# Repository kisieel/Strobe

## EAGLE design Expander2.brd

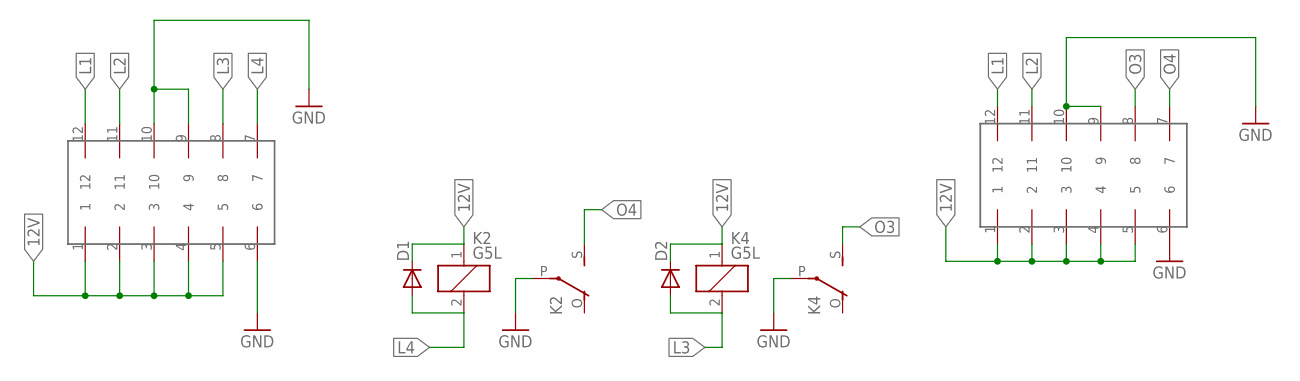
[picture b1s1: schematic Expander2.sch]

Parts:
D1, D2: DIODESMB; SMB-DIODE
IN: MF42-10
K2, K4: G5L; G5LE
OUT: MF42-10

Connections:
12V: D1.C, D2.C, IN.1, IN.2, IN.3, IN.4, IN.5, K2.1, K4.1, OUT.1, OUT.2, OUT.3, OUT.4, OUT.5
GND: IN.6, IN.9, IN.10, K2.P, K4.P, OUT.6, OUT.9, OUT.10
L1: IN.12, OUT.12
L2: IN.11, OUT.11
L3: D2.A, IN.8, K4.2
L4: D1.A, IN.7, K2.2
O3: K4.S, OUT.8
O4: K2.S, OUT.7

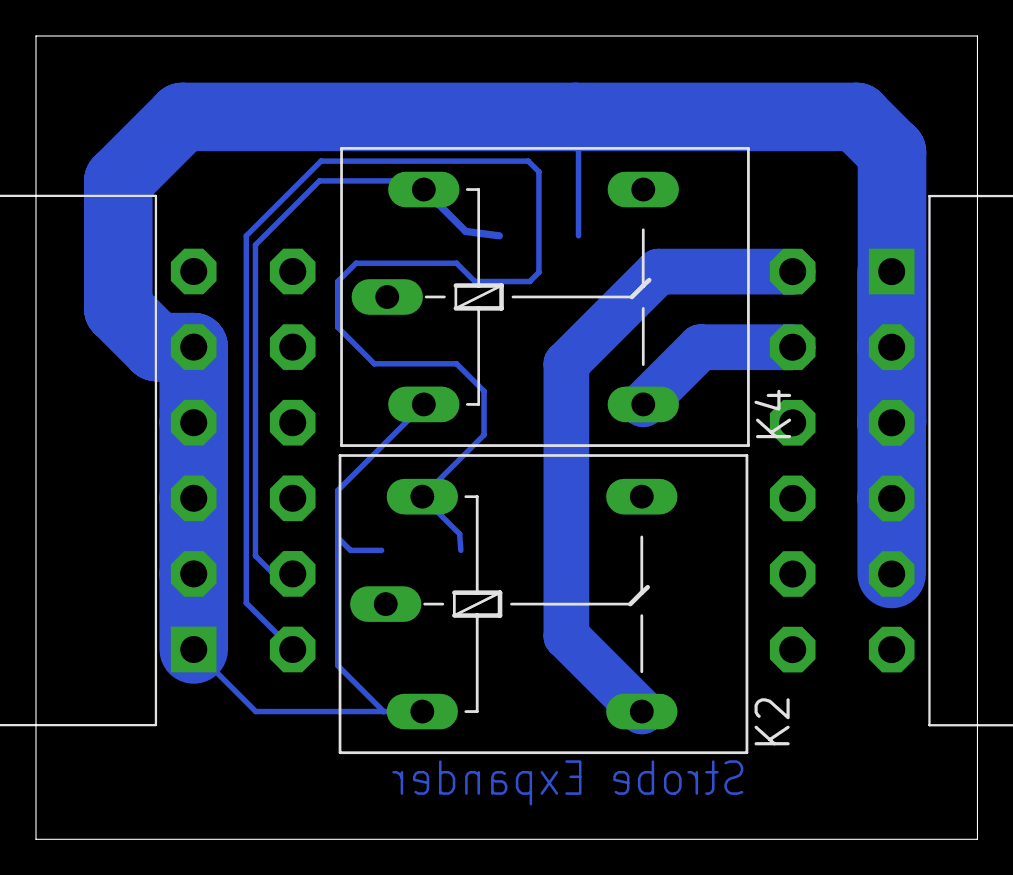
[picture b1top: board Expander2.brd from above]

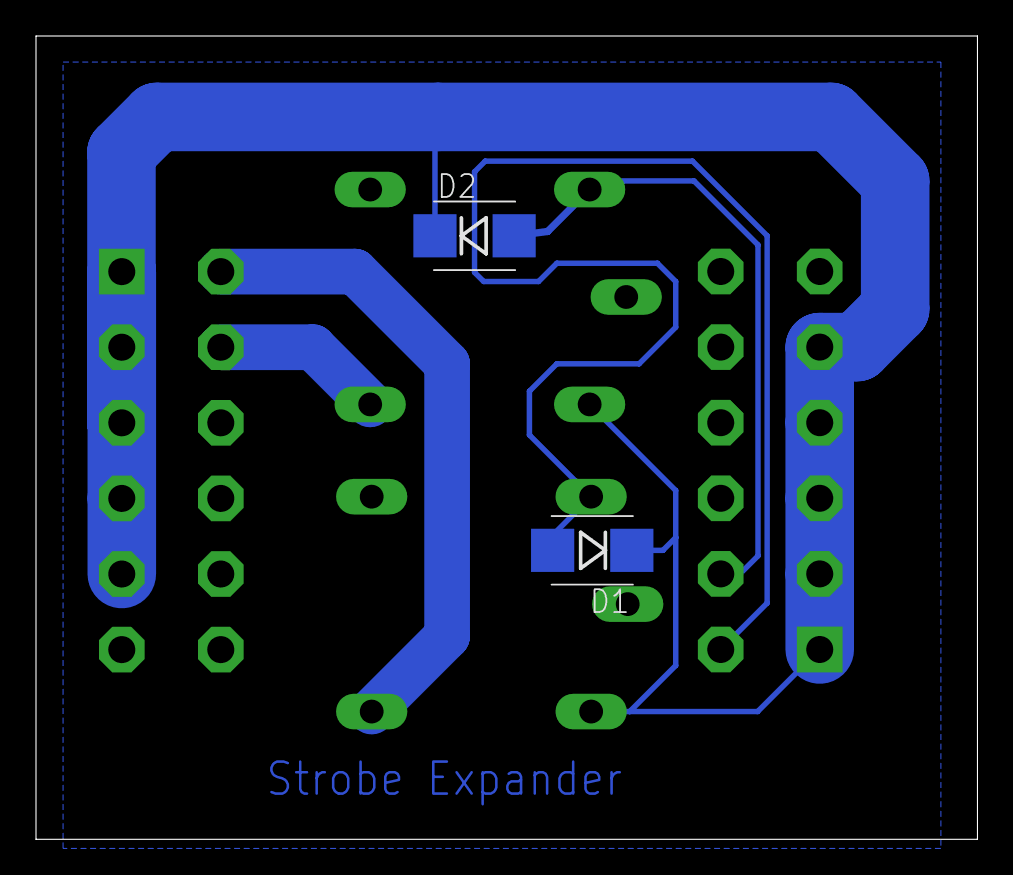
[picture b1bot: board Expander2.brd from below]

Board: 2 copper layers, 52.3 x 44.6 mm, 6 parts (2 on the bottom side), 8 nets.

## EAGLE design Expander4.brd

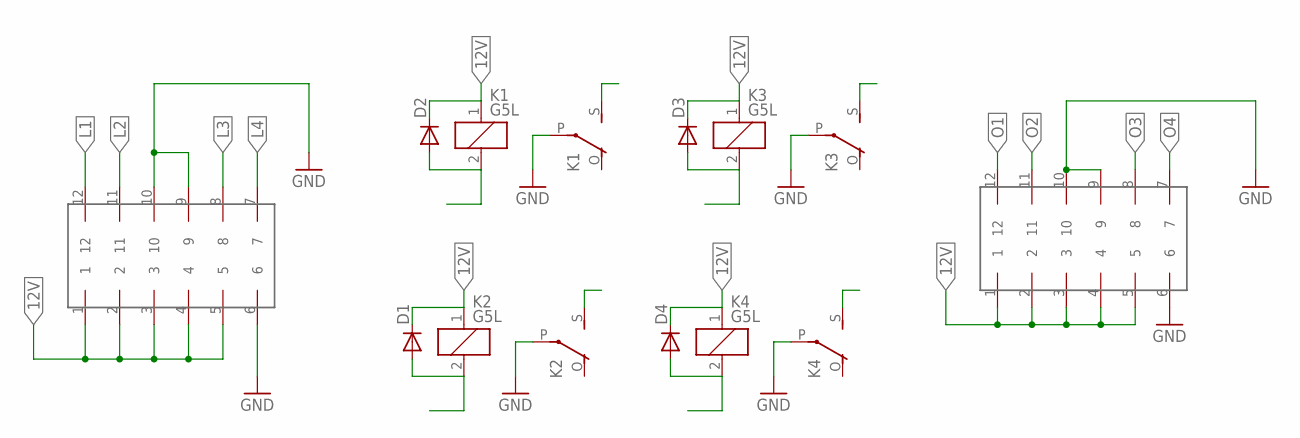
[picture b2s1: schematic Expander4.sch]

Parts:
D1, D2, D3, D4: DIODESMB; SMB-DIODE
IN: MF42-10
K1, K2, K3, K4: G5L; G5LE
OUT: MF42-10

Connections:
12V: D1.C, D2.C, D3.C, D4.C, IN.1, IN.2, IN.3, IN.4, IN.5, K1.1, K2.1, K3.1, K4.1, OUT.1, OUT.2, OUT.3, OUT.4, OUT.5
GND: IN.6, IN.9, IN.10, K1.P, K2.P, K3.P, K4.P, OUT.6, OUT.9, OUT.10
L1: D2.A, IN.12, K1.2
L2: D1.A, IN.11, K2.2
L3: D3.A, IN.8, K3.2
L4: D4.A, IN.7, K4.2
O1: K1.S, OUT.12
O2: K2.S, OUT.11
O3: K3.S, OUT.8
O4: K4.S, OUT.7

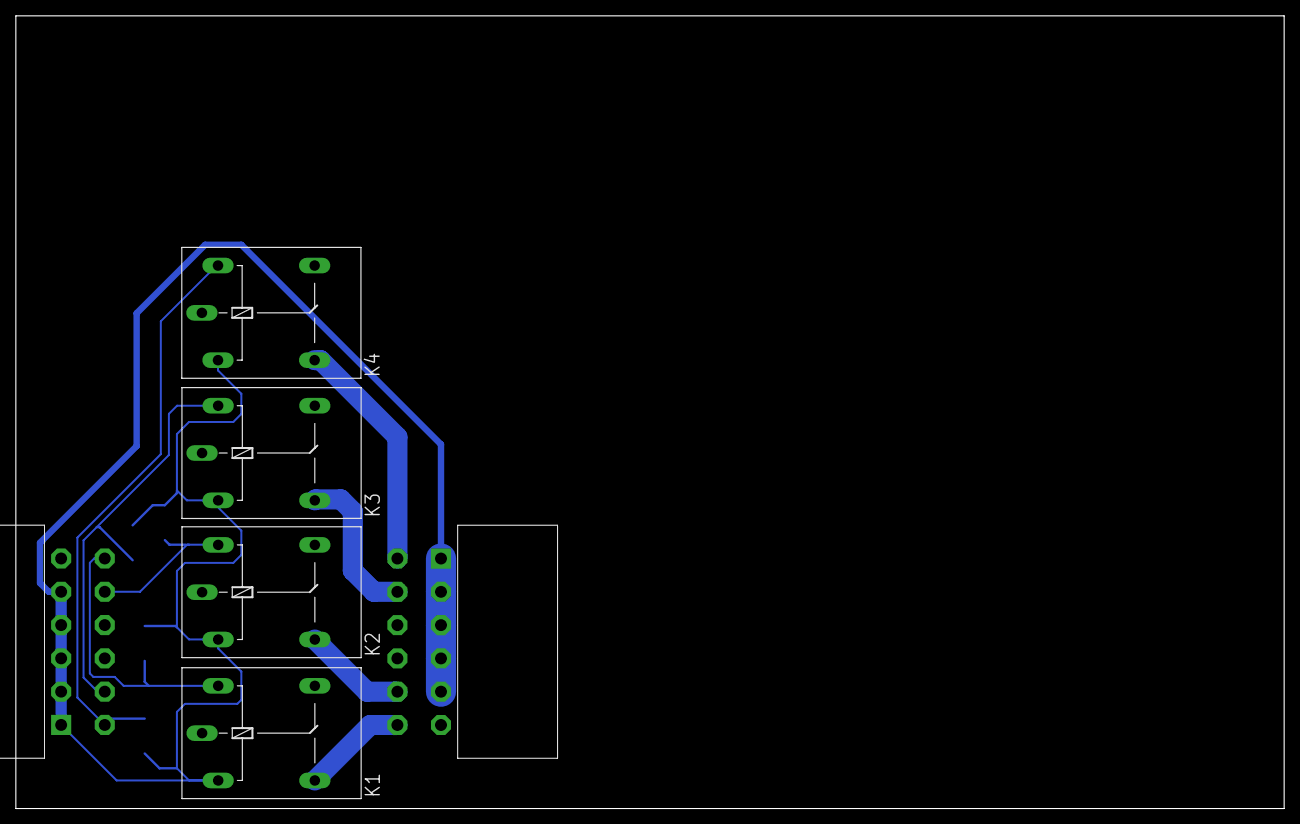
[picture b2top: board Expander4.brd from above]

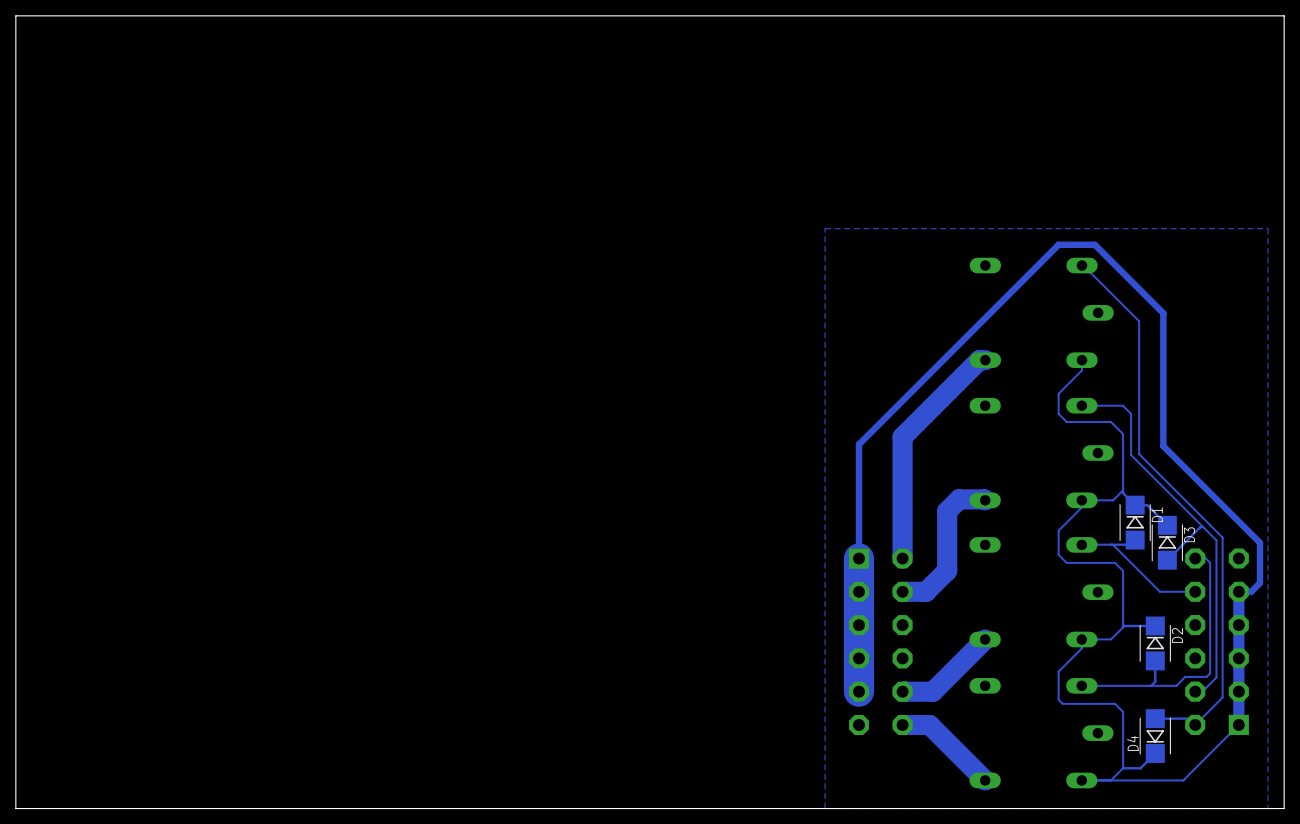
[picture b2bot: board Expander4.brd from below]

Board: 2 copper layers, 160.0 x 100.0 mm, 10 parts (4 on the bottom side), 10 nets.

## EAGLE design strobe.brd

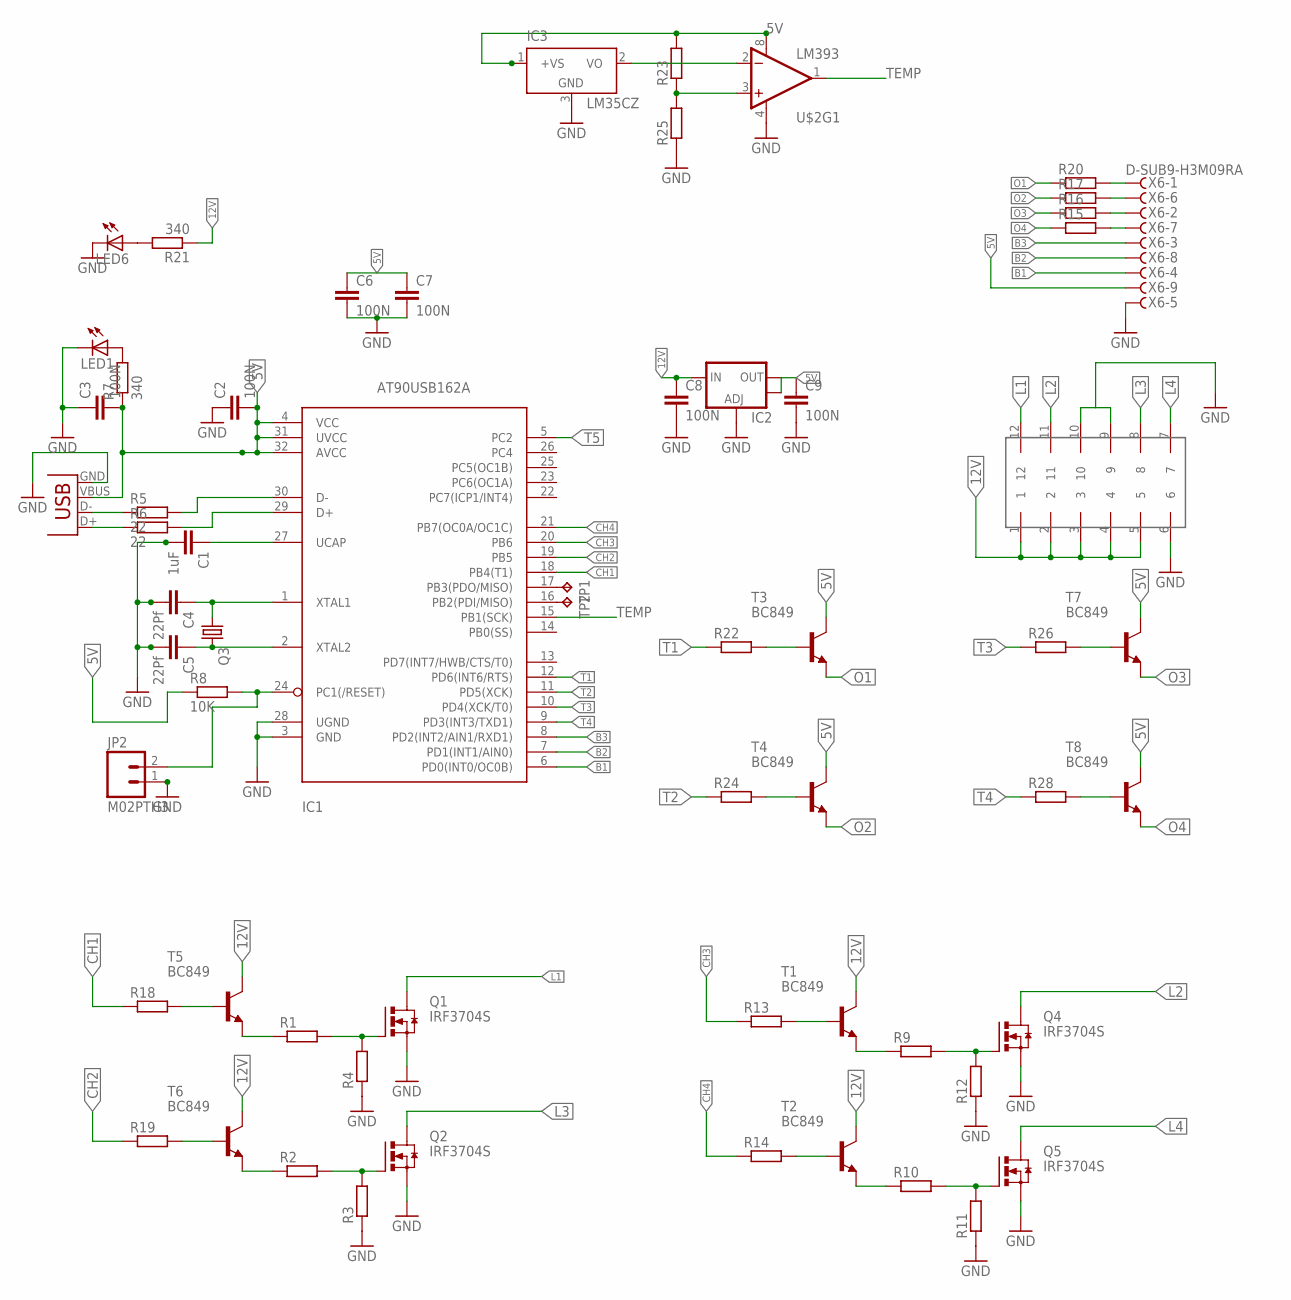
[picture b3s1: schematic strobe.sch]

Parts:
C1: 1uF; C0805
C2, C3, C6, C7, C8, C9: 100N; C0805
C4, C5: 22Pf; C0603
IC1: AT90USB162A; TQFP32-08
IC2: V_REG_LM1117SOT223; SOT223
IC3: LM35CZ; TO92
JP1: USB-B; USB-B-PTH
JP2: M02PTH3; 1X02_LONGPADS
LED1, LED6: LEDSML0805; SML0805
Q1, Q2, Q4, Q5: IRF3704S; D2PACK
Q3: CRYSTALSM49; SM49
R1, R2, R3, R4, R9, R10, R11, R12, R13, R14, R15, R16, R17, R18, R19, R20, R22, R24, R26, R28: R-EU_R0805; R0805
R5, R6: 22; R0805
R7, R21: 340; R0805
R8: 10K; R0805
R23, R25: R-EU_M0805; M0805
T1, T2, T3, T4, T5, T6, T7, T8: BC849; SOT23
TP1, TP2: TPB1,27; B1,27
U$1: MF42-10
U$2: LM393; SO08
X6: D-SUB9-H3M09RA; H3M09RA

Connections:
5V: C2.2, C3.2, C6.1, C7.1, C9.1, IC1.4 (VCC), IC1.31 (UVCC), IC1.32 (AVCC), IC2.2 (OUT), IC2.4 (OUT), IC3.1 (+VS), JP1.VBUS, R7.1, R8.1, R23.2, T3.3 (C), T4.3 (C), T7.3 (C), T8.3 (C), U$2.8 (V+), X6.9
12V: C8.1, IC2.3 (IN), R21.1, T1.3 (C), T2.3 (C), T5.3 (C), T6.3 (C), U$1.1, U$1.2, U$1.3, U$1.4, U$1.5
B1: IC1.6 (PD0(INT0/OC0B)), X6.4
B2: IC1.7 (PD1(INT1/AIN0)), X6.8
B3: IC1.8 (PD2(INT2/AIN1/RXD1)), X6.3
CH1: IC1.18 (PB4(T1)), R18.1
CH2: IC1.19 (PB5), R19.1
CH3: IC1.20 (PB6), R13.1
CH4: IC1.21 (PB7(OC0A/OC1C)), R14.1
GND: C1.2, C2.1, C3.1, C4.2, C5.2, C6.2, C7.2, C8.2, C9.2, IC1.3 (GND), IC1.28 (UGND), IC2.1 (ADJ), IC3.3 (GND), JP1.GND, JP2.1, LED1.C, LED6.C, Q1.3 (S), Q2.3 (S), Q4.3 (S), Q5.3 (S), R3.1, R4.1, R11.1, R12.1, R25.1, U$1.6, U$1.9, U$1.10, U$2.4 (V-), X6.5
L1: Q1.2 (D), U$1.12
L2: Q4.2 (D), U$1.11
L3: Q2.2 (D), U$1.8
L4: Q5.2 (D), U$1.7
unnamed: Q1.1 (G), R1.2, R4.2
unnamed: Q2.1 (G), R2.2, R3.2
unnamed: IC3.2 (VO), U$2.2 (-IN)
unnamed: R23.1, R25.2, U$2.3 (+IN)
unnamed: C1.1, IC1.27 (UCAP)
unnamed: JP1.D+, R6.1
unnamed: JP1.D-, R5.1
unnamed: IC1.30 (D-), R5.2
unnamed: IC1.29 (D+), R6.2
unnamed: LED1.A, R7.2
unnamed: Q4.1 (G), R9.2, R12.2
unnamed: C5.1, IC1.2 (XTAL2), Q3.2
unnamed: C4.1, IC1.1 (XTAL1), Q3.1
unnamed: IC1.24 (PC1(/RESET)), JP2.2, R8.2
unnamed: Q5.1 (G), R10.2, R11.2
unnamed: R9.1, T1.2 (E)
unnamed: R10.1, T2.2 (E)
unnamed: R13.2, T1.1 (B)
unnamed: R14.2, T2.1 (B)
unnamed: IC1.17 (PB3(PDO/MISO)), TP1.TP
unnamed: LED6.A, R21.2
unnamed: R22.2, T3.1 (B)
unnamed: IC1.16 (PB2(PDI/MISO)), TP2.TP
unnamed: R20.2, X6.1
unnamed: R24.2, T4.1 (B)
unnamed: R1.1, T5.2 (E)
unnamed: R2.1, T6.2 (E)
unnamed: R18.2, T5.1 (B)
unnamed: R19.2, T6.1 (B)
unnamed: R17.2, X6.6
unnamed: R26.2, T7.1 (B)
unnamed: R16.2, X6.2
unnamed: R15.2, X6.7
unnamed: R28.2, T8.1 (B)
O1: R20.1, T3.2 (E)
O2: R17.1, T4.2 (E)
O3: R16.1, T7.2 (E)
O4: R15.1, T8.2 (E)
T1: IC1.12 (PD6(INT6/RTS)), R22.1
T2: IC1.11 (PD5(XCK)), R24.1
T3: IC1.10 (PD4(XCK/T0)), R26.1
T4: IC1.9 (PD3(INT3/TXD1)), R28.1
T5: IC1.5 (PC2)
TEMP: IC1.15 (PB1(SCK)), U$2.1 (OUT)

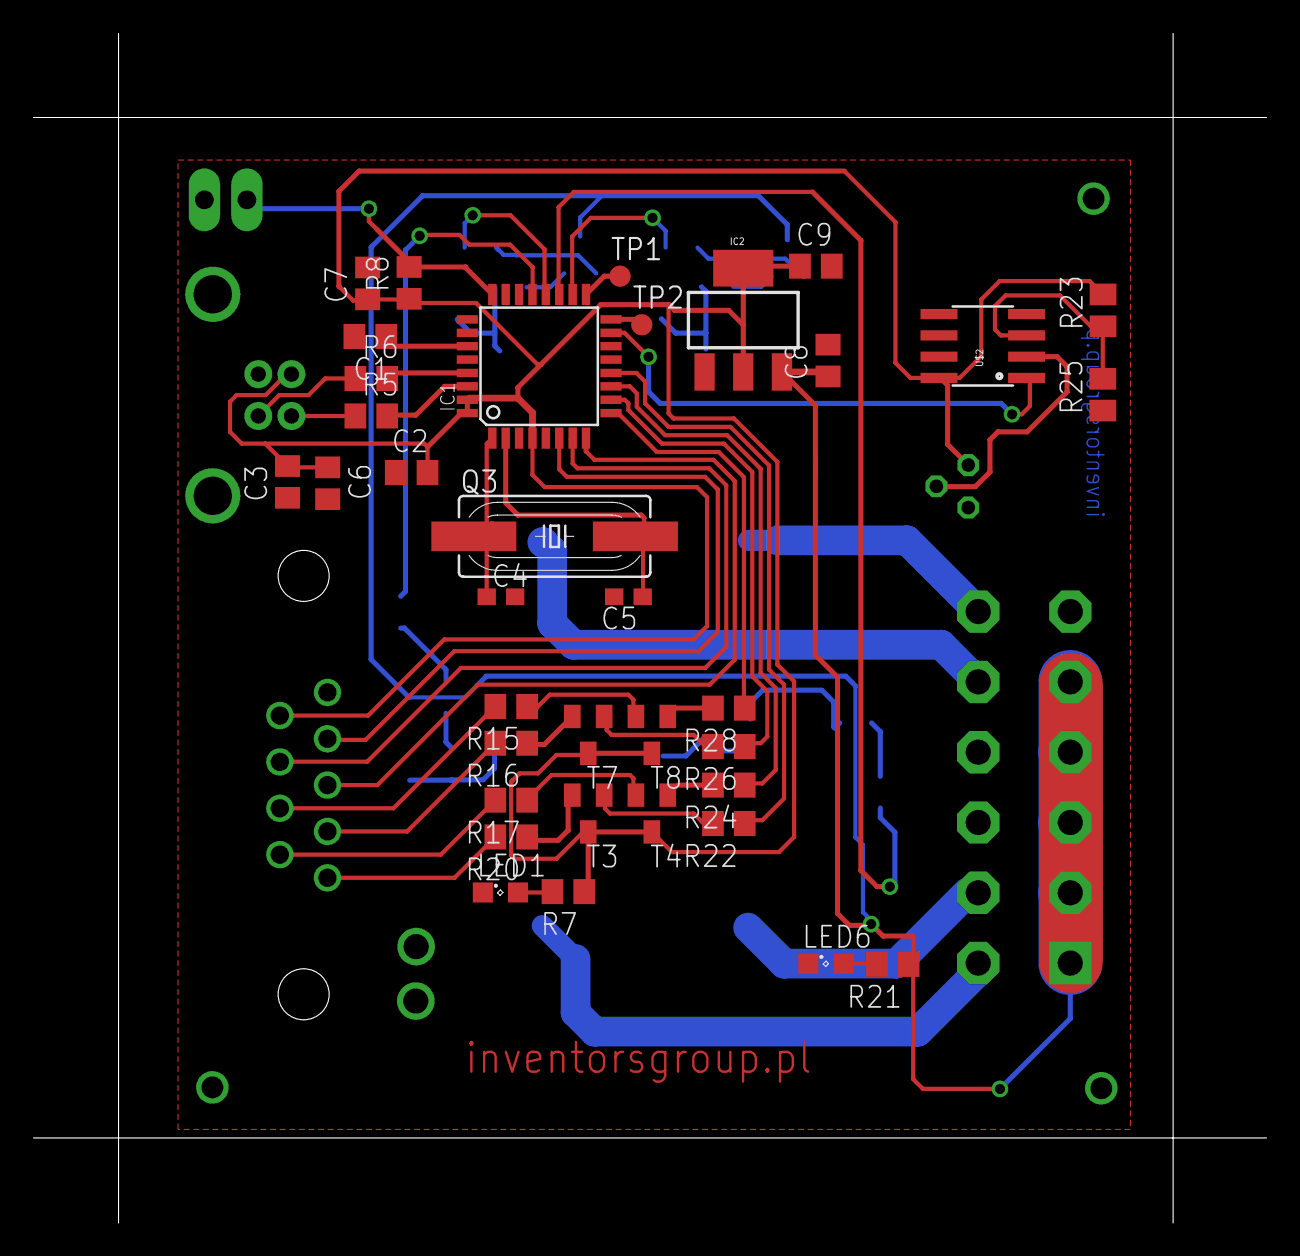
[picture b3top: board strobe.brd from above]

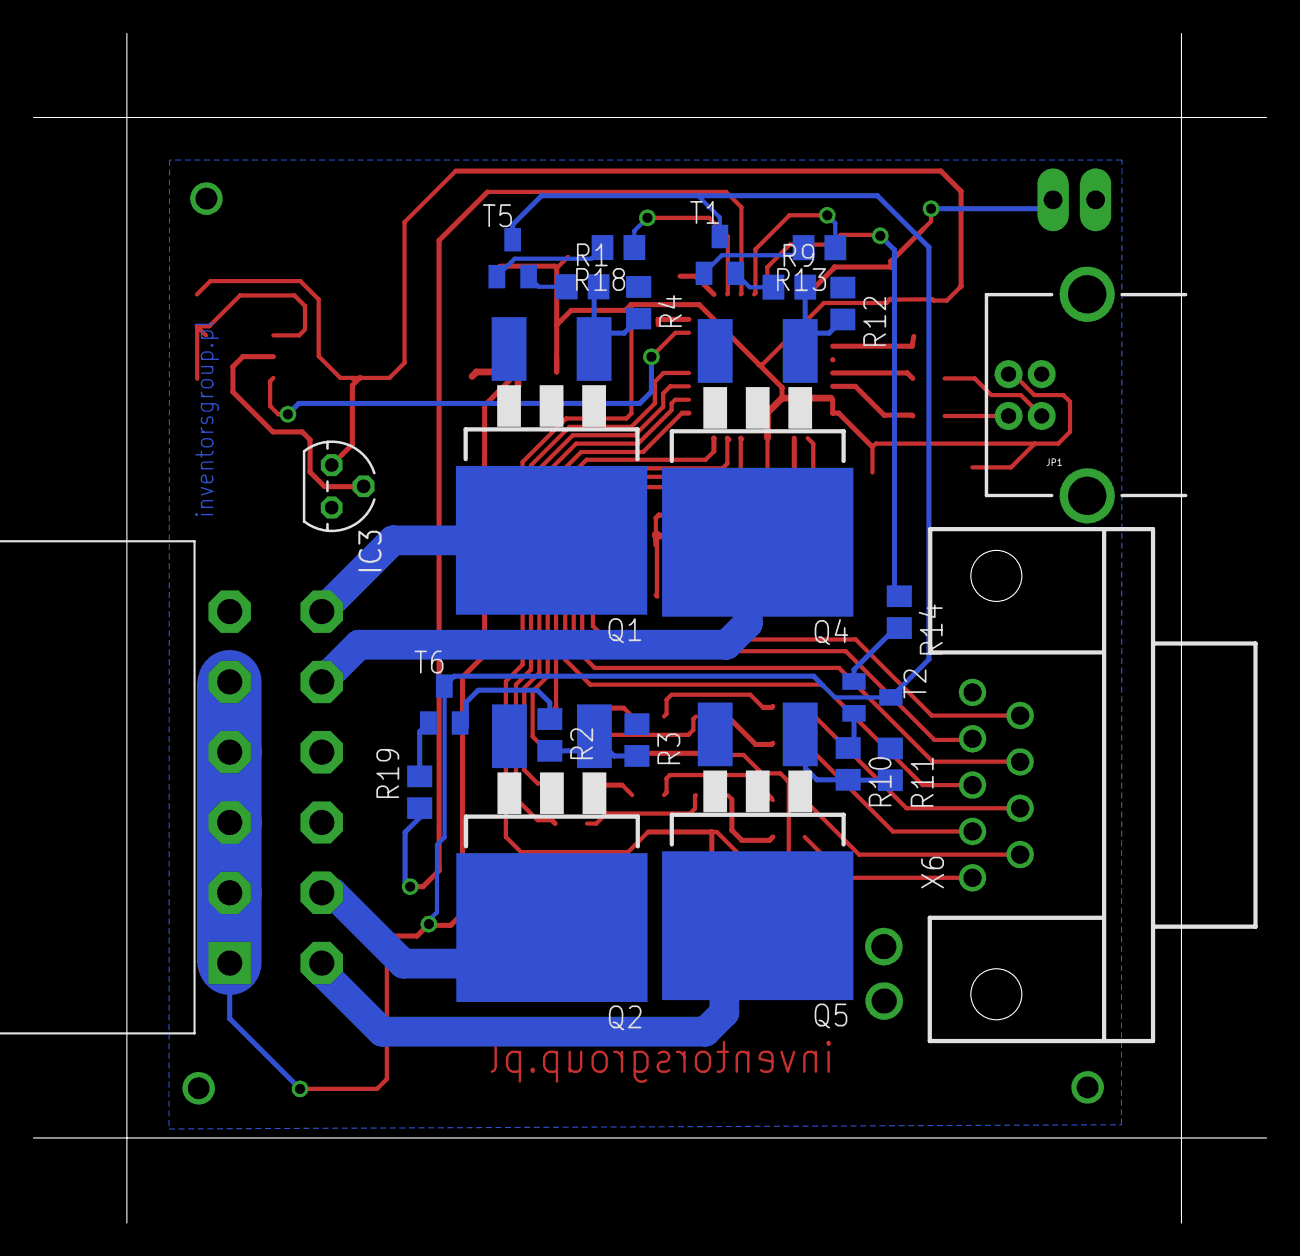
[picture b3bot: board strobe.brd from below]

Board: 2 copper layers, 73.7 x 71.1 mm, 61 parts (24 on the bottom side), 57 nets.

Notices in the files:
parts and their libraries:
SparkFun-DiscreteSemi: Licensing: CC v3.0 Share-Alike You are welcome to use this library for commercial purposes.
